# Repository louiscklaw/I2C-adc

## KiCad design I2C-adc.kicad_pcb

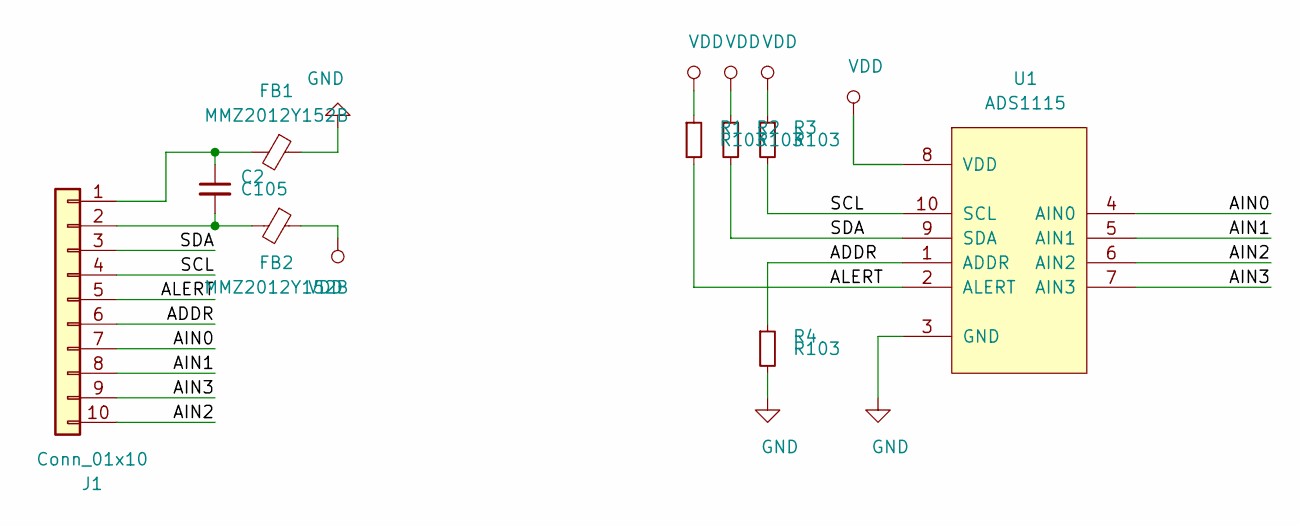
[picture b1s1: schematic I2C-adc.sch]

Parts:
C2: C105; C_0805_2012Metric_Pad1.15x1.40mm_HandSolder
FB1, FB2: MMZ2012Y152B; L_0805_2012Metric_Pad1.15x1.40mm_HandSolder
J1: Conn_01x10; PinHeader_1x10_P2.54mm_Vertical
R1, R2, R3, R4: R103; R_0805_2012Metric_Pad1.15x1.40mm_HandSolder
U1: ADS1115; MSOP-10_3x3mm_P0.5mm

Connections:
/ADDR: J1.6, R4.1, U1.1 (ADDR)
/AIN0: J1.7, U1.4 (AIN0)
/AIN1: J1.8, U1.5 (AIN1)
/AIN2: J1.10, U1.6 (AIN2)
/AIN3: J1.9, U1.7 (AIN3)
/ALERT: J1.5, R1.2, U1.2 (ALERT)
/SCL: J1.4, R3.2, U1.10 (SCL)
/SDA: J1.3, R2.2, U1.9 (SDA)
GND: FB1.1, R4.2, U1.3 (GND)
unnamed: C2.1, FB1.2, J1.1
unnamed: C2.2, FB2.2, J1.2
VDD: FB2.1, R1.1, R2.1, R3.1, U1.8 (VDD)

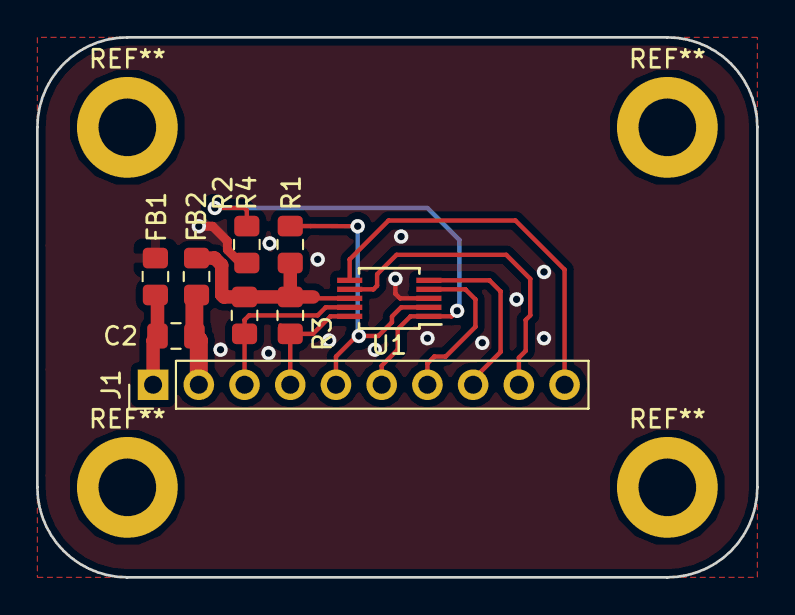
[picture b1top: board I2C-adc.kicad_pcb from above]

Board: 2 copper layers, 40.0 x 30.0 mm, 9 parts (0 on the bottom side), 12 nets.

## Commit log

2018-10-18 update,
2020-05-05 ci: init travis build config,
2020-05-05 ci: init travis token,
